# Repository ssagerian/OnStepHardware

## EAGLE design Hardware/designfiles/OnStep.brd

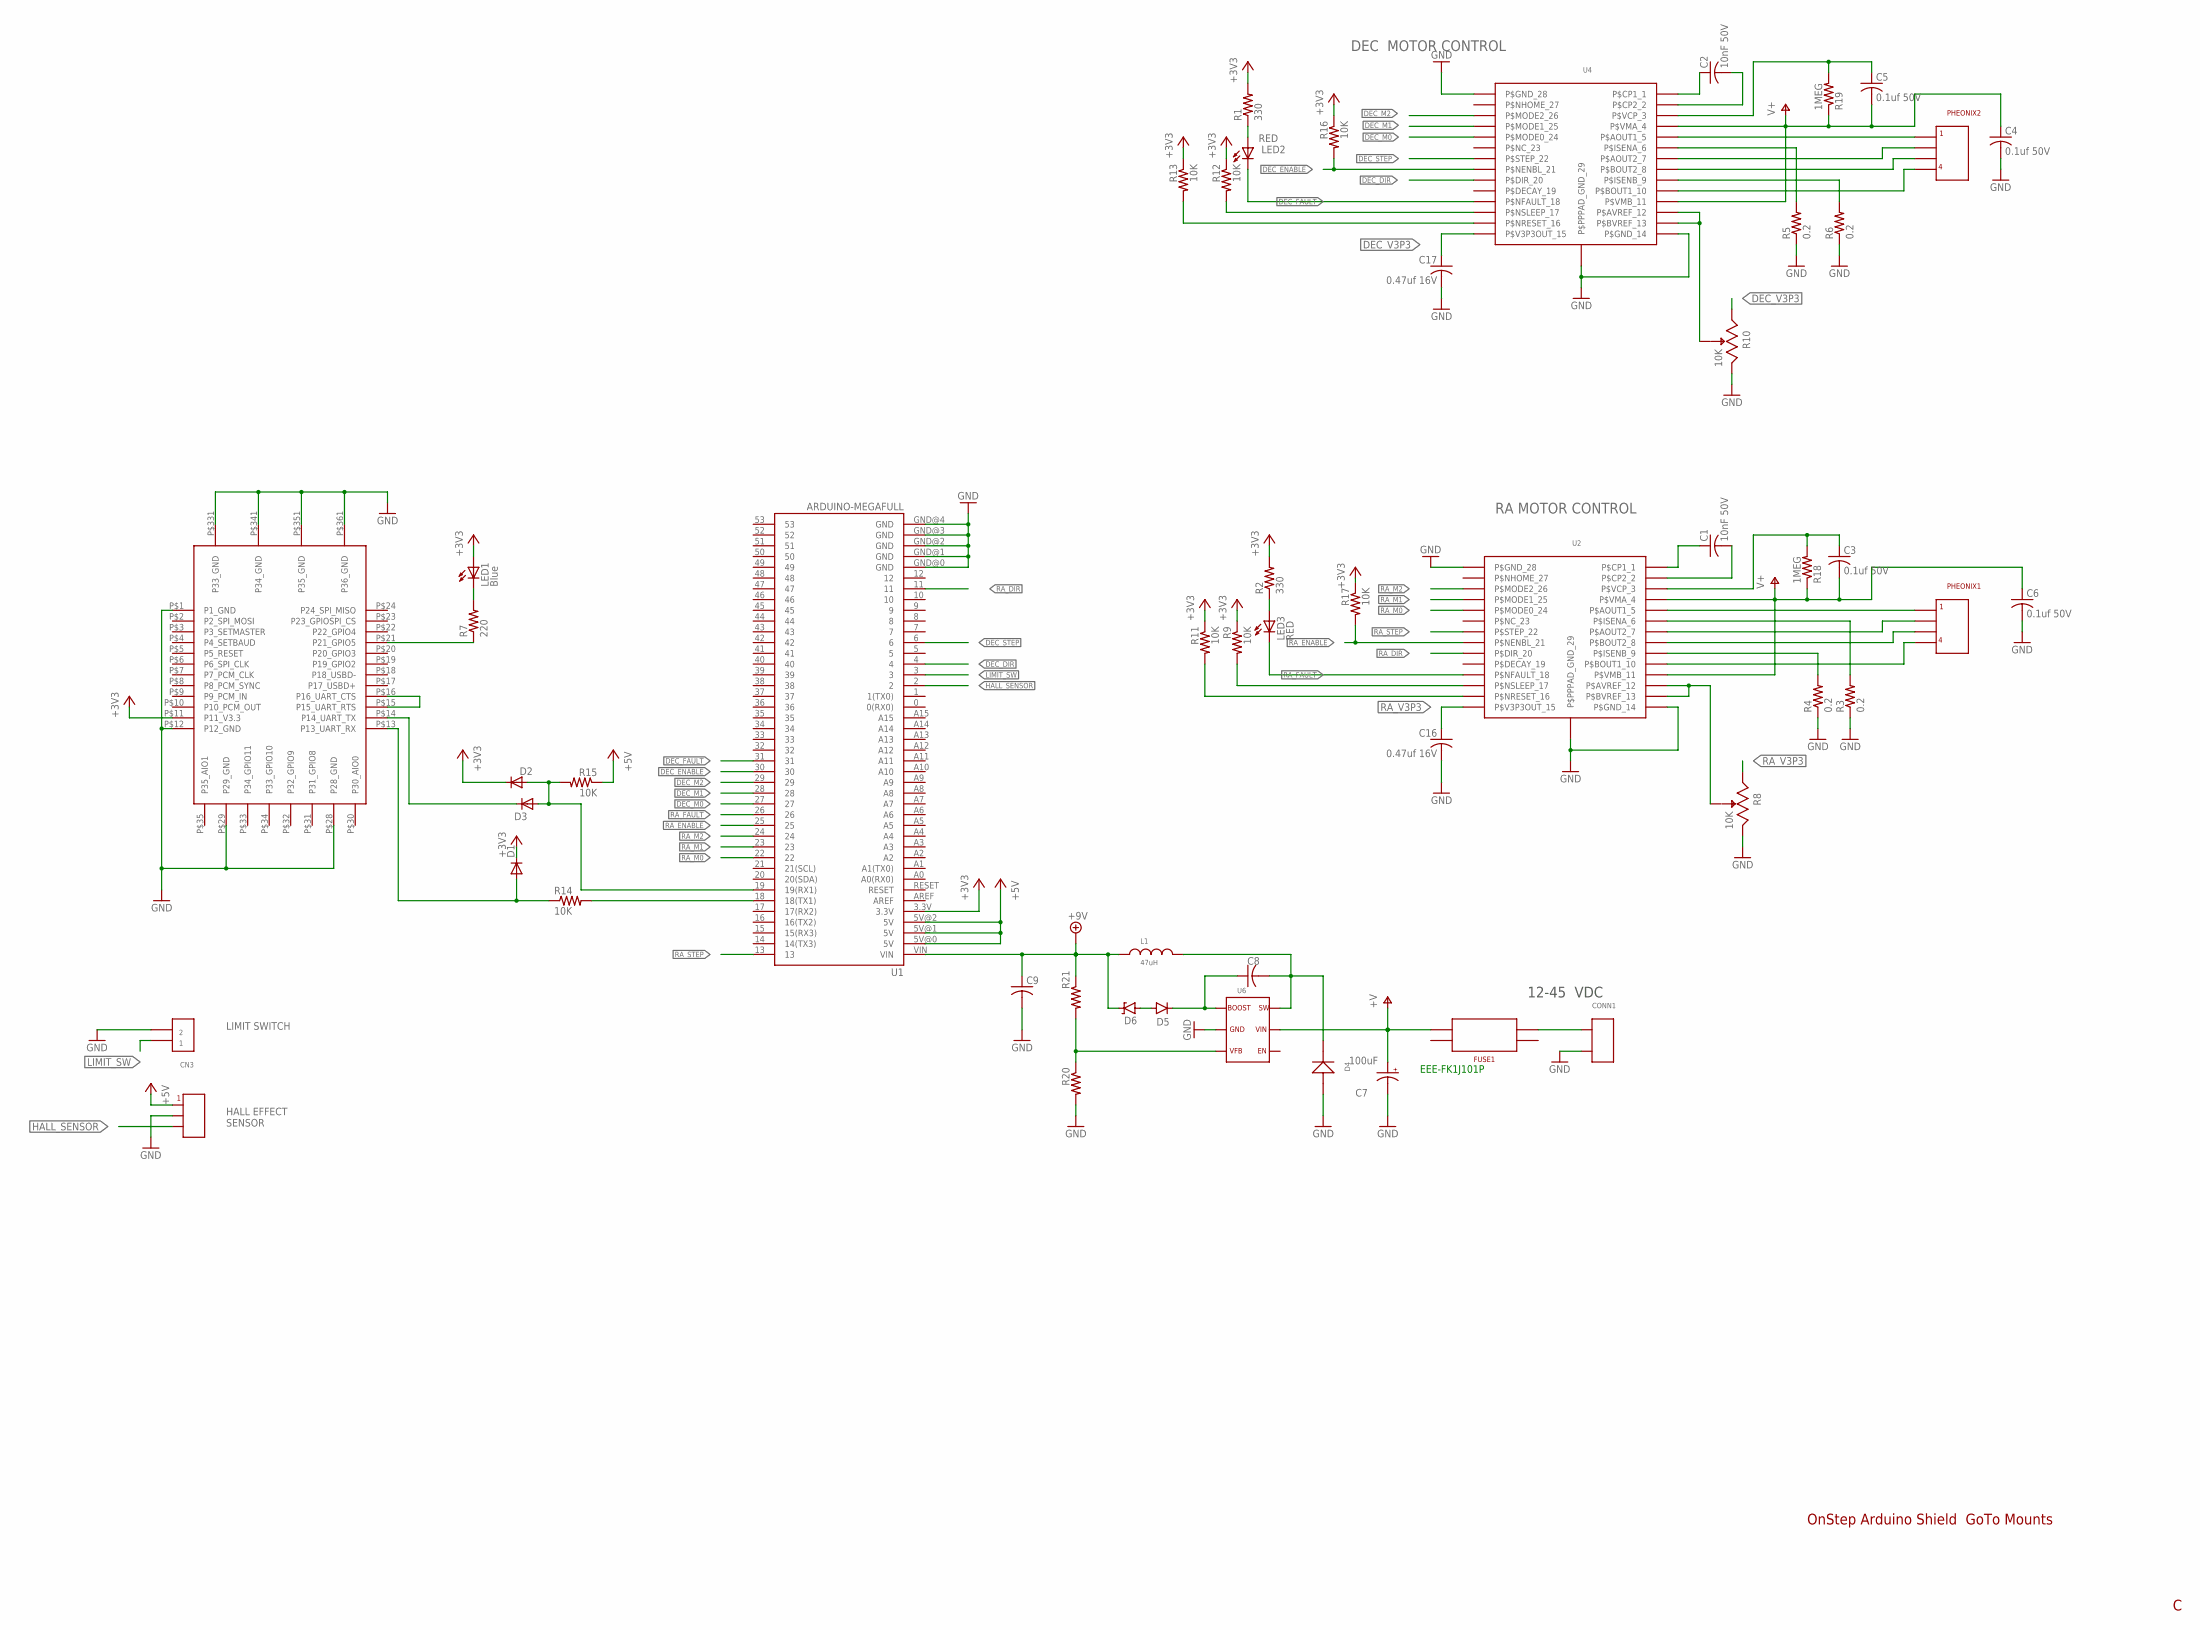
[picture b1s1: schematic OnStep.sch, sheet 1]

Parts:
C1, C2: 10nF 50V; C0805
C3, C4, C5, C6: 0.1uf 50V; C0805
C7: 100uF; PANASONIC_G
C8: 100nf; C0805
C9: 10uf 0805 x5r; C0805
C16, C17: 0.47uf 16V; C0805
CN3: B2B-PH
CONN1: PHEONIX2; PHOENIX2
CONN2: B3B-PH
D1, D2, D3: 1N4148; SOD323-W
D4: B2100; SMB
D5: 1N4148; SOD-323
D6: 7.3V; SOD-323
FUSE1: MINI_FUSE_SMT; MINI_FUSE_HOLDER_SMT
L1: 47uH; WURTH_7MMX7MM_INDUCTOR
LED1: Blue; LED0805
LED2, LED3: RED; CHIPLED_0805
PHEONIX1, PHEONIX2: PHEONIX_4PIN; PHENIOX
R1, R2: 330; R0805
R3, R4, R5, R6: 0.2; R0805
R7: 220; R0805
R8, R10: 10K; BOURN3362P
R9, R11, R12, R13, R14, R15, R16, R17, R20: 10K; R0805
R18, R19: 1MEG; R0805
R21: 102K 1%; R0805
U1: ARDUINO-MEGAFULL; ARDUINO_MEGA
U2, U4: DRV8825
U3: RN42QFP; RN42QFN
U6: MCP16331; SOT23-6

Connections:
+3V3: D1.C, D2.C, LED1.1 (A), R1.2, R2.2, R9.1, R11.1, R12.1, R13.1, R16.1, R17.1, U1.3.3V, U3.P$11 (P11_V3.3)
+5V: CONN2.P$1, R15.1, U1.5V@0 (5V), U1.5V@1 (5V), U1.5V@2 (5V)
+9V: C9.1, D6.C, L1.P$1, R21.1, U1.VIN
+24V: C3.2, C4.1, C5.2, C6.1, C7.+, FUSE1.P$1, R18.1, R19.1, U2.P$4 (P$VMA_4), U2.P$11 (P$VMB_11), U4.P$4 (P$VMA_4), U4.P$11 (P$VMB_11), U6.5
DEC_A1: PHEONIX2.P$1, U4.P$5 (P$AOUT1_5)
DEC_A2: PHEONIX2.P$2, U4.P$7 (P$AOUT2_7)
DEC_B1: PHEONIX2.P$4, U4.P$10 (P$BOUT1_10)
DEC_B2: PHEONIX2.P$3, U4.P$8 (P$BOUT2_8)
DEC_DIR: U1.4, U4.P$20 (P$DIR_20)
DEC_ENABLE: R16.2, U1.30, U4.P$21 (P$NENBL_21)
DEC_FAULT: LED2.C, U1.31, U4.P$18 (P$NFAULT_18)
DEC_M0: U1.27, U4.P$24 (P$MODE0_24)
DEC_M1: U1.28, U4.P$25 (P$MODE1_25)
DEC_M2: U1.29, U4.P$26 (P$MODE2_26)
DEC_STEP: U1.6, U4.P$22 (P$STEP_22)
DEC_V3P3: C17.1, R10.P$1, U4.P$15 (P$V3P3OUT_15)
GND: C4.2, C6.2, C7.-, C9.2, C16.2, C17.2, CN3.P$2, CONN1.P$3, CONN2.P$2, D4.A, R3.1, R4.1, R5.1, R6.1, R8.P$3, R10.P$3, R20.2, U1.GND@0 (GND), U1.GND@1 (GND), U1.GND@2 (GND), U1.GND@3 (GND), U1.GND@4 (GND), U2.P$14 (P$GND_14), U2.P$28 (P$GND_28), U2.P$29 (P$PPPAD_GND_29), U3.P$1 (P1_GND), U3.P$12 (P12_GND), U3.P$28 (P28_GND), U3.P$29 (P29_GND), U3.P$331 (P33_GND), U3.P$341 (P34_GND), U3.P$351 (P35_GND), U3.P$361 (P36_GND), U4.P$14 (P$GND_14), U4.P$28 (P$GND_28), U4.P$29 (P$PPPAD_GND_29), U6.2
HALL_SENSOR: CONN2.P$3, U1.2
LIMIT_SW: CN3.P$1, U1.3
unnamed: R14.2, U1.18 (18(TX1))
unnamed: C1.1, U2.P$1 (P$CP1_1)
unnamed: C1.2, U2.P$2 (P$CP2_2)
unnamed: R20.1, R21.2, U6.3
unnamed: R12.2, U4.P$17 (P$NSLEEP_17)
unnamed: R13.2, U4.P$16 (P$NRESET_16)
unnamed: R11.2, U2.P$16 (P$NRESET_16)
unnamed: R9.2, U2.P$17 (P$NSLEEP_17)
unnamed: LED3.A, R2.1
unnamed: R3.2, U2.P$6 (P$ISENA_6)
unnamed: R4.2, U2.P$9 (P$ISENB_9)
unnamed: LED2.A, R1.1
unnamed: C8.1, D5.C, U6.1
unnamed: D5.A, D6.A
unnamed: R5.2, U4.P$6 (P$ISENA_6)
unnamed: R6.2, U4.P$9 (P$ISENB_9)
unnamed: C2.1, U4.P$1 (P$CP1_1)
unnamed: C2.2, U4.P$2 (P$CP2_2)
unnamed: C3.1, R18.2, U2.P$3 (P$VCP_3)
unnamed: C5.1, R19.2, U4.P$3 (P$VCP_3)
unnamed: R10.P$2, U4.P$12 (P$AVREF_12), U4.P$13 (P$BVREF_13)
unnamed: R8.P$2, U2.P$12 (P$AVREF_12), U2.P$13 (P$BVREF_13)
unnamed: D1.A, R14.1, U3.P$13 (P13_UART_RX)
unnamed: C8.2, D4.C, L1.P$2, U6.6
unnamed: D3.C, U3.P$14 (P14_UART_TX)
unnamed: D2.A, D3.A, R15.2, U1.19 (19(RX1))
unnamed: U3.P$15 (P15_UART_RTS), U3.P$16 (P16_UART_CTS)
unnamed: LED1.2 (C), R7.2
unnamed: R7.1, U3.P$21 (P21_GPIO5)
RA_A1: PHEONIX1.P$1, U2.P$5 (P$AOUT1_5)
RA_A2: PHEONIX1.P$2, U2.P$7 (P$AOUT2_7)
RA_B1: PHEONIX1.P$4, U2.P$10 (P$BOUT1_10)
RA_B2: PHEONIX1.P$3, U2.P$8 (P$BOUT2_8)
RA_DIR: U1.11, U2.P$20 (P$DIR_20)
RA_ENABLE: R17.2, U1.25, U2.P$21 (P$NENBL_21)
RA_FAULT: LED3.C, U1.26, U2.P$18 (P$NFAULT_18)
RA_M0: U1.22, U2.P$24 (P$MODE0_24)
RA_M1: U1.23, U2.P$25 (P$MODE1_25)
RA_M2: U1.24, U2.P$26 (P$MODE2_26)
RA_STEP: U1.13, U2.P$22 (P$STEP_22)
RA_V3P3: C16.1, R8.P$1, U2.P$15 (P$V3P3OUT_15)
V+: CONN1.P$2, FUSE1.P$3

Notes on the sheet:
12-45 VDC
RA MOTOR CONTROL
DEC MOTOR CONTROL
LIMIT SWITCH
HALL EFFECT SENSOR
OnStep Arduino Shield GoTo Mounts
EEE-FK1J101P

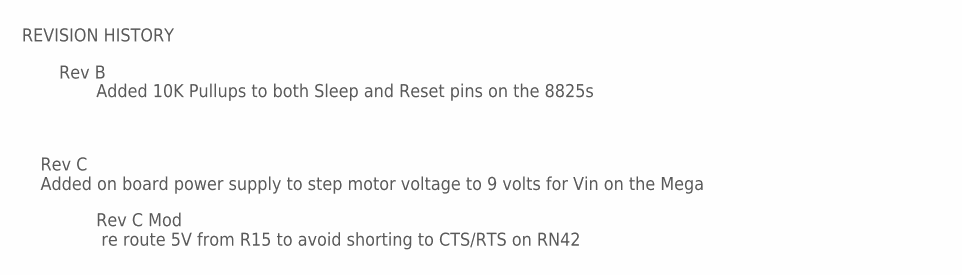
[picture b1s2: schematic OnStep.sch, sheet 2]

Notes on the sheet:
REVISION HISTORY
Added 10K Pullups to both Sleep and Reset pins on the 8825s
Rev B
Rev C Added on board power supply to step motor voltage to 9 volts for Vin on the Mega
Rev C Mod re route 5V from R15 to avoid shorting to CTS/RTS on RN42

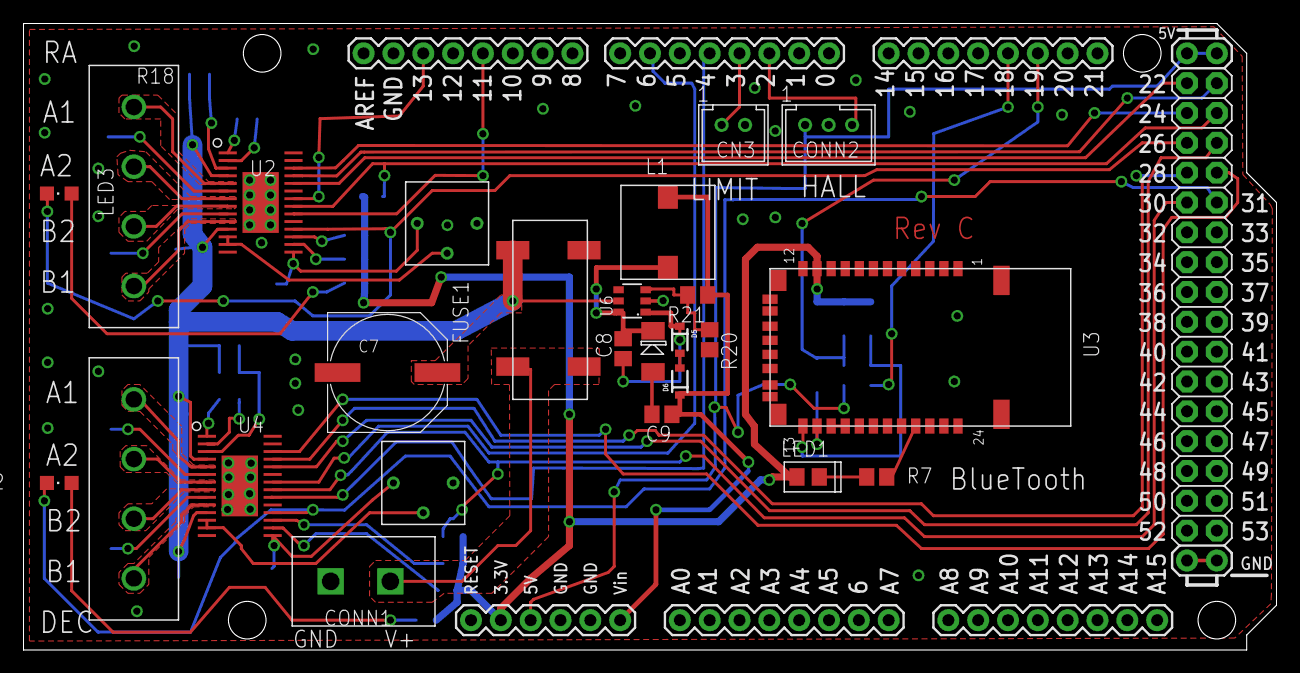
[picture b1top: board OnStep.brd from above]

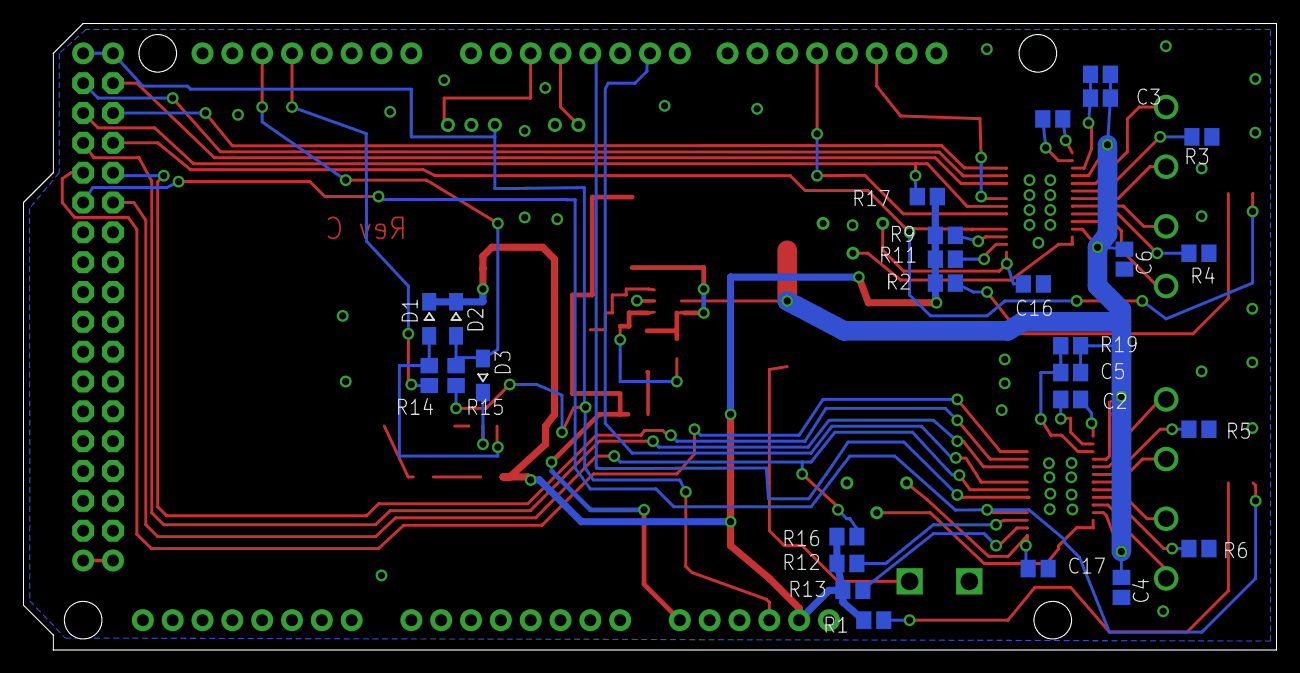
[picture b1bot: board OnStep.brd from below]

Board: 2 copper layers, 106.7 x 53.3 mm, 53 parts (27 on the bottom side), 61 nets.

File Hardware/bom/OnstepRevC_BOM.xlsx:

Build Quantity | 10
Part | Value | Quantity Per Board | Quantity Per Build | Device | Manufacture | Manufacture PN | Digikey | Package | Description
C1,C2 | 10nF 50V | 2 | 20 | C-USC0805 | TDK | CGA4C2C0G1H103J060AA | 445-6947-1-ND | C0805 | CAPACITOR, American symbol
C3,C4,C5,C6,C8 | 0.1uf 50V | 5 | 50 | C-USC0805 | Kemet | C0805C104K5RACTU | 399-1170-1-ND | C0805 | CAPACITOR, American symbol
C16,C17 | 0.47uf 16V | 2 | 20 | C-USC0805 | Kemet | C0805C474K4RACTU | 399-8099-1-ND | C0805 | CAPACITOR, American symbol
C7 | 100uF | 1 | 10 | CPOL-USG | Pansonic | EEE-FK1J101P | PCE3819CT-ND | PANASONIC_G | POLARIZED CAPACITOR, American symbol
C9 | 10uf | 1 | 10 |  | Samsung | CL21A106KAYNNNE | 1276-2891-1-ND | C0805
CN3 |  | 1 | 10 | B2B-PH | JST Sales | B2B-PH-K-S(LF)(SN) | 455-1704-ND
CONN1 |  | 1 | 10 | PHEONIX2 | Wurth | 691216510002 | 732-2749-ND
CONN2 |  | 1 | 10 | B3B-PH | JST Sales | B3B-PH-K-S(LF)(SN) | 455-1705-ND
D1,D2,D3,D5 |  | 4 | 40 | 1N4148 | Diodes Inc | 1N4148WS-7-F | 1N4148WS-FDICT-ND | SOD323-W | DIODE
FUSE1 |  | 1 | 10 | MINI_FUSE_SMT | Keystone | 3588 | 3588K-ND | MINI_FUSE_HOLDER_SMT
LED1 | Blue | 1 | 10 | LED0805 | Wurth | 150080BS75000 | 732-4982-1-ND | LED0805
LED2,LED3 | RED | 2 | 20 | LEDCHIPLED_0805 | Wurth | 150080RS75000 | 732-4984-1-ND | CHIPLED_0805 | LED
PHEONIX1,PHEONIX2 |  | 2 | 20 | PHEONIX_4PIN | Wurth | 691311500104 | 732-2060-ND
R1,R2 | 330 | 2 | 20 | R-US_R0805 | Pansonic | ERJ-6ENF3300V | P330CCT-ND | R0805 | RESISTOR, American symbol
R3,R4,R5,R6 | 0.2 | 4 | 40 | R-US_R0805 | Pansonic | ERJ-S6SFR20V | P.2BJCT-ND | R0805 | RESISTOR, American symbol
R7 | 220 | 1 | 10 | R-US_R0805 | Pansonic | ERJ-6ENF2200V | P220CCT-ND | R0805 | RESISTOR, American symbol
R9,R11,R12,R13,R14,R16,R16,R17,R20 | 10K CHIP | 8 | 80 | R0805 | Pansonic | ERJ-6ENF1002V | P10KACT-ND | R0805
R21 | 102K | 1 | 10 |  | Pansonic | ERJ-6ENF1023V | P102KCCT-ND | R0805
R8,R10 | 10K POT | 2 | 20 | BOURNTRIMPOT | Bourns | 3362P-1-103LF | 3362P-103LF-ND | 10K trimmer Pot
R18,R19 | 1MEG | 2 | 20 | R-US_R0805 | Pansonic | ERJ-6ENF1004V | P1.00MCCT-ND | R0805 | RESISTOR, American symbol
U2,U4 |  | 2 | 20 | DRV8825 | TI | DRV8825PWPR | 296-29503-1-ND | 28 PIN HTSSOP
U3 |  | 1 | 10 | RN42QFP | Microchip | RN42 | 740-1038-ND | RN42QFN
Plug for RA and DEC |  | 2 | 20 |  | Wurth | 691351500004 | 732-2042-ND
58V 5 A fuse |  | 1 | 10 |  | Little Fuse Inc | 0997005.WXN | F1873-ND | mini fuse
D4 |  | 1 | 10 |  | Diodes Inc | B2100-13-F | B2100-FDICT-ND | D0-214AA SMB
U6 | switching ps | 1 | 10 |  | Microchip | MCP16331T-E | MCP16331T-E/CHCT-ND
L1 | inductor | 1 | 10 |  | Wurth | 7447779147W | 732-4272-1-ND
D6 | 7.5V Zener | 1 | 10 |  | Diodes Inc | MMSZ5236BS-7-F | MMSZ5236BS-FDICT-ND | SOD323

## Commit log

2015-06-29 :confetti_ball: Added .gitattributes
2015-06-29 Rev C
    Rev C added the onboard switchmode power supply for powering the Arduino
    independent of the usb cable.

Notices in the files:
parts and their libraries:
SparkFun-Boards: Licensing: Creative Commons ShareAlike 4.0 International - https://creativecommons.org/licenses/by-sa/4.0
